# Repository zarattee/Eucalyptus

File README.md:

# Eucalyptus
 La tarjeta Eucalyptus es una placa diseñada principalmente para robots minisumos de competencia.

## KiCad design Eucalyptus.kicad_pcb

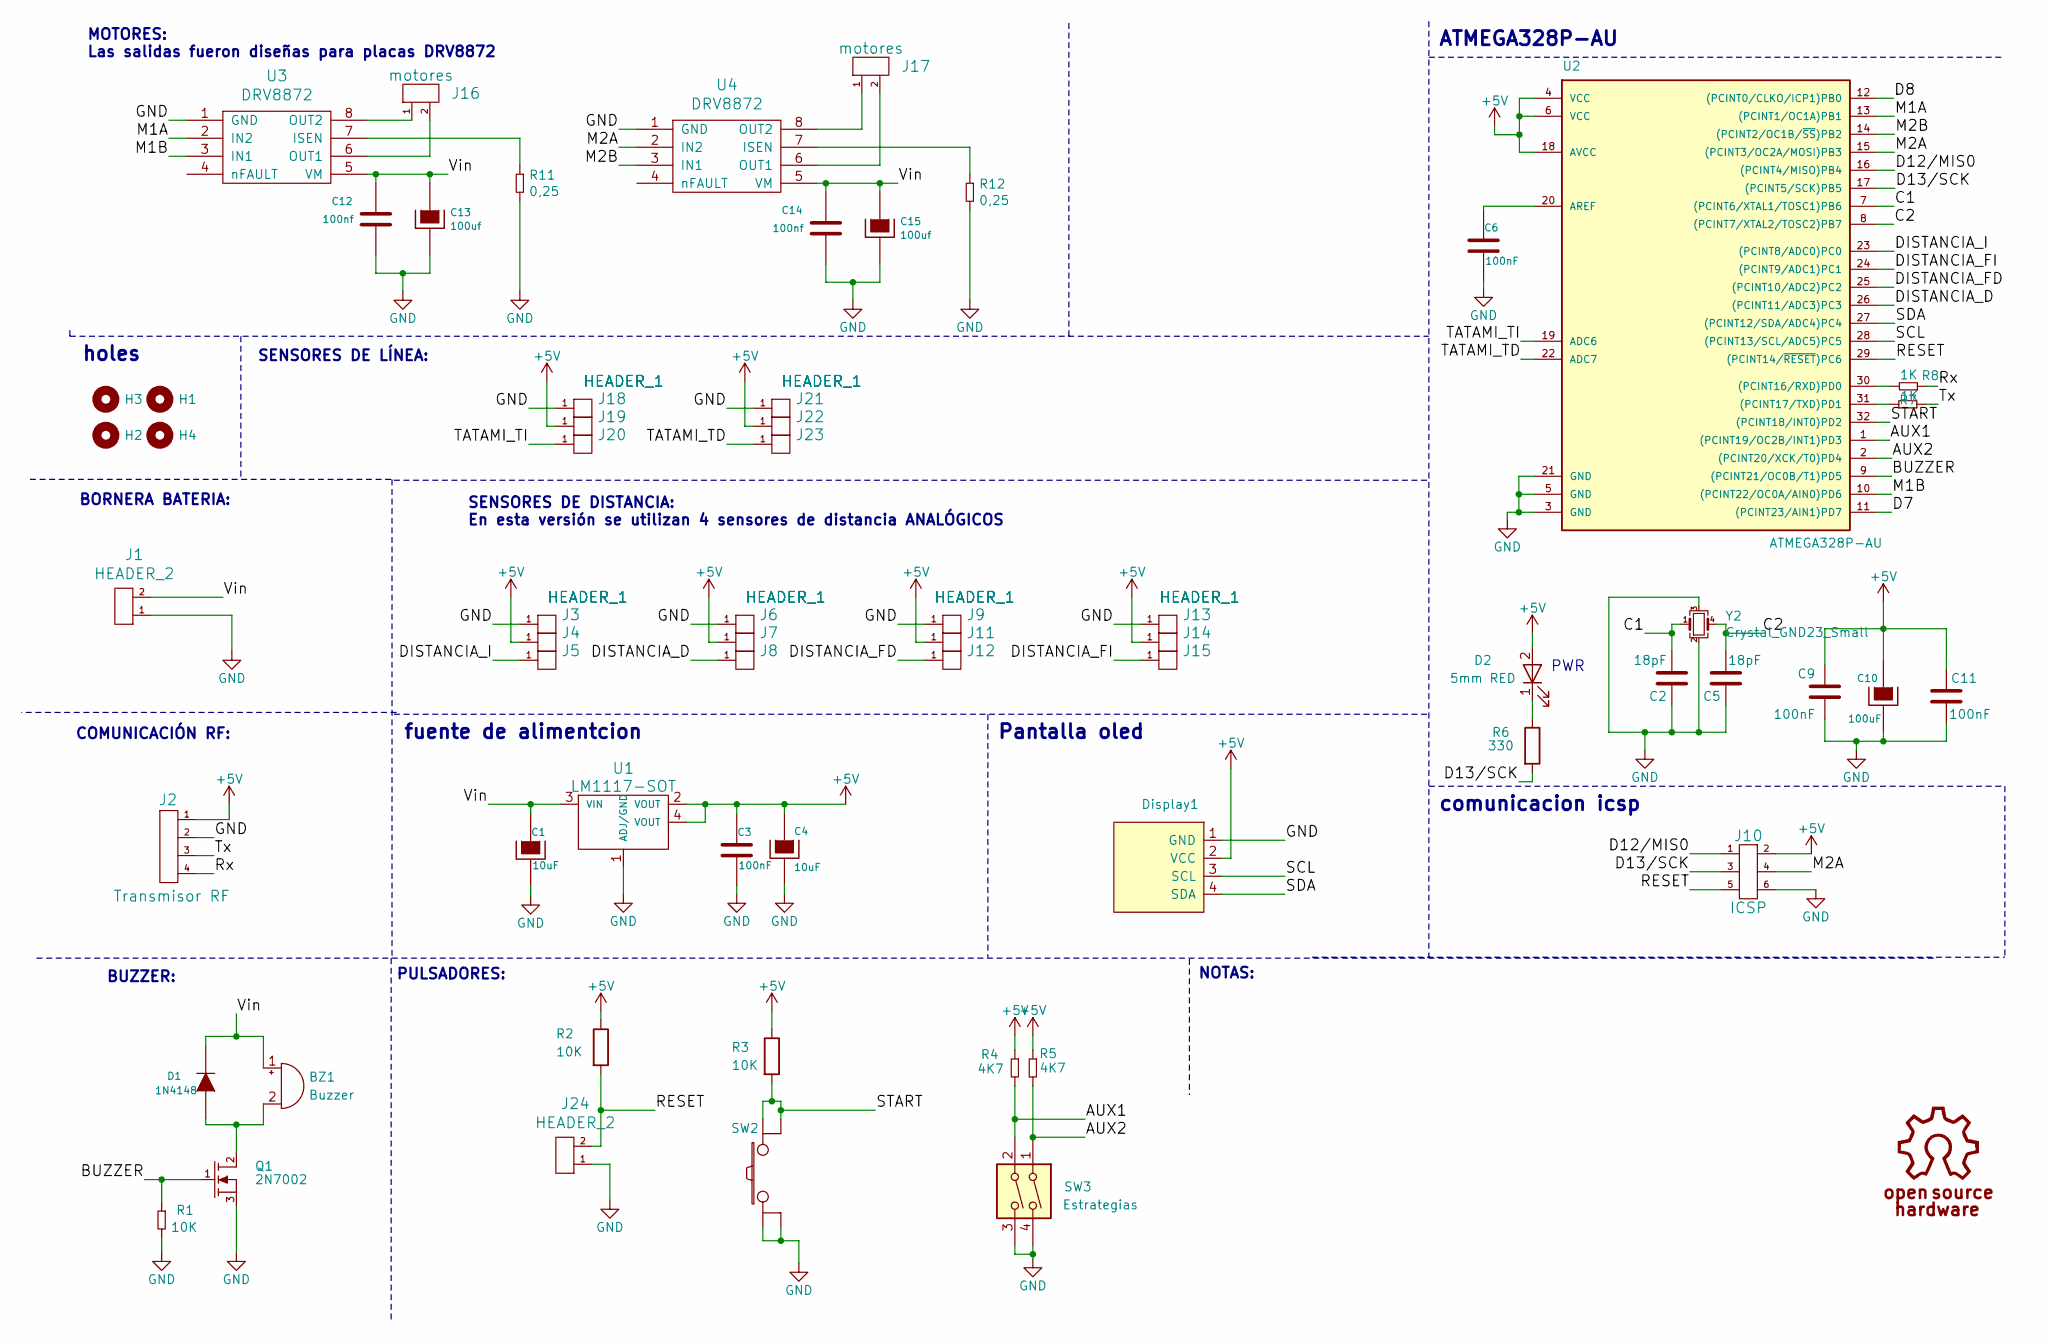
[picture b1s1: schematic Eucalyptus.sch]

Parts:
BZ1: Buzzer; Buzzer_12mm
C1, C4: 10uF; CAP_ELEC_SMD_4X5.5
C2, C5: 18pF; C_1206
C3, C6, C9, C11: 100nF; C_1206
C10: 100uF; CAP_ELEC_SMD_4X5.5
C12, C14: 100nf; C_1206
C13, C15: 100uf; CAP_ELEC_SMD_4X5.5
D1: 1N4148; SOD80C
D2: 5mm RED; LED_1206
Display1: SSD1306-SSD1306-128x64_OLED; 128x64OLED
H1, H2, H3, H4: Mounting_Hole; Separador_M3_5mm
J1: HEADER_2; JST_EH_B2B-EH-A_1x02_P2.50mm_Vertical
J2: Transmisor RF; pin_strip_4
J3, J4, J5, J6, J7, J8, J9, J11, J12, J13, J14, J15, J18, J19, J20, J21, J22, J23: HEADER_1; DUAL_PAD_TH_SMD_2x5mm
J10: ICSP; pin_strip_3x2
J16, J17: motores; JST_EH_B2B-EH-A_1x02_P2.50mm_Vertical
J24: HEADER_2; SW_SPST_EVQPE1
Q1: 2N7002; SOT23
R1, R2, R3: 10K; R_1206
R4, R5: 4K7; R_1206
R6: 330; R_1206
R7, R8: 1K; R_1206
R11, R12: 0,25; R_1206
SW2: SW_PUSH; Pulsador_TH_4
SW3: Estrategias; Dip_SW_2-300
U1: LM1117-SOT; SOT223
U2: ATMEGA328P-AU; TQFP-32_7x7mm_Pitch0.8mm
U3, U4: DRV8872; SSOP-8
Y2: Crystal_GND23_Small; Crystal_SMD_EuroQuartz_X22-4Pin_2.5x2.0mm

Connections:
+5V: C3.1, C4.1, C9.2, C10.1, C11.2, D2.2 (A), Display1.2 (VCC), J2.1, J4.1, J7.1, J10.2, J11.1, J14.1, J19.1, J22.1, R2.1, R3.1, R4.1, R5.1, U1.2 (VOUT), U1.4 (VOUT), U2.4 (VCC), U2.6 (VCC), U2.18 (AVCC)
/AUX1: R4.2, SW3.2, U2.1 ((PCINT19/OC2B/INT1)PD3)
/AUX2: R5.2, SW3.1, U2.2 ((PCINT20/XCK/T0)PD4)
/BUZZER: Q1.1 (G), R1.1, U2.9 ((PCINT21/OC0B/T1)PD5)
/C1: C2.2, U2.7 ((PCINT6/XTAL1/TOSC1)PB6), Y2.1
/C2: C5.2, U2.8 ((PCINT7/XTAL2/TOSC2)PB7), Y2.4
/D12/MIS0: J10.1, U2.16 ((PCINT4/MISO)PB4)
/D13/SCK: J10.3, R6.2, U2.17 ((PCINT5/SCK)PB5)
/DISTANCIA_D: J8.1, U2.26 ((PCINT11/ADC3)PC3)
/DISTANCIA_FD: J12.1, U2.25 ((PCINT10/ADC2)PC2)
/DISTANCIA_FI: J15.1, U2.24 ((PCINT9/ADC1)PC1)
/DISTANCIA_I: J5.1, U2.23 ((PCINT8/ADC0)PC0)
/M1A: U2.13 ((PCINT1/OC1A)PB1), U3.2 (IN2)
/M1B: U2.10 ((PCINT22/OC0A/AIN0)PD6), U3.3 (IN1)
/M2A: J10.4, U2.15 ((PCINT3/OC2A/MOSI)PB3), U4.2 (IN2)
/M2B: U2.14 ((PCINT2/OC1B/~SS~)PB2), U4.3 (IN1)
/RESET: J10.5, J24.2, R2.2, U2.29 ((PCINT14/~RESET~)PC6)
/Rx: J2.4, R8.1
/SCL: Display1.3 (SCL), U2.28 ((PCINT13/SCL/ADC5)PC5)
/SDA: Display1.4 (SDA), U2.27 ((PCINT12/SDA/ADC4)PC4)
/START: R3.2, SW2.3, SW2.4, U2.32 ((PCINT18/INT0)PD2)
/TATAMI_TD: J23.1, U2.22 (ADC7)
/TATAMI_TI: J20.1, U2.19 (ADC6)
/Tx: J2.3, R7.1
/Vin: BZ1.1 (-), C1.1, C12.1, C13.1, C14.1, C15.1, D1.2 (K), J1.2, U1.3 (VIN), U3.5 (VM), U4.5 (VM)
GND: C1.2, C2.1, C3.2, C4.2, C5.1, C6.2, C9.1, C10.2, C11.1, C12.2, C13.2, C14.2, C15.2, Display1.1 (GND), J1.1, J2.2, J3.1, J6.1, J9.1, J10.6, J13.1, J18.1, J21.1, J24.1, Q1.3 (S), R1.2, R11.2, R12.2, SW2.1, SW2.2, SW3.3, SW3.4, U1.1 (ADJ/GND), U2.3 (GND), U2.5 (GND), U2.21 (GND), U3.1 (GND), U4.1 (GND), Y2.2, Y2.3
unnamed: BZ1.2 (+), D1.1 (A), Q1.2 (D)
unnamed: C6.1, U2.20 (AREF)
unnamed: D2.1 (K), R6.1
unnamed: J16.1, U3.8 (OUT2)
unnamed: J16.2, U3.6 (OUT1)
unnamed: J17.1, U4.8 (OUT2)
unnamed: J17.2, U4.6 (OUT1)
unnamed: R7.2, U2.31 ((PCINT17/TXD)PD1)
unnamed: R8.2, U2.30 ((PCINT16/RXD)PD0)
unnamed: R11.1, U3.7 (ISEN)
unnamed: R12.1, U4.7 (ISEN)

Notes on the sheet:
NOTAS:
SENSORES DE LÍNEA:
COMUNICACIÓN RF:
SENSORES DE DISTANCIA: En esta versión se utilizan 4 sensores de distancia ANALÓGICOS
BORNERA BATERIA:
MOTORES: Las salidas fueron diseñas para placas DRV8872
PULSADORES:
PWR
BUZZER:
Pantalla oled
comunicacion icsp
ATMEGA328P-AU
fuente de alimentcion
holes

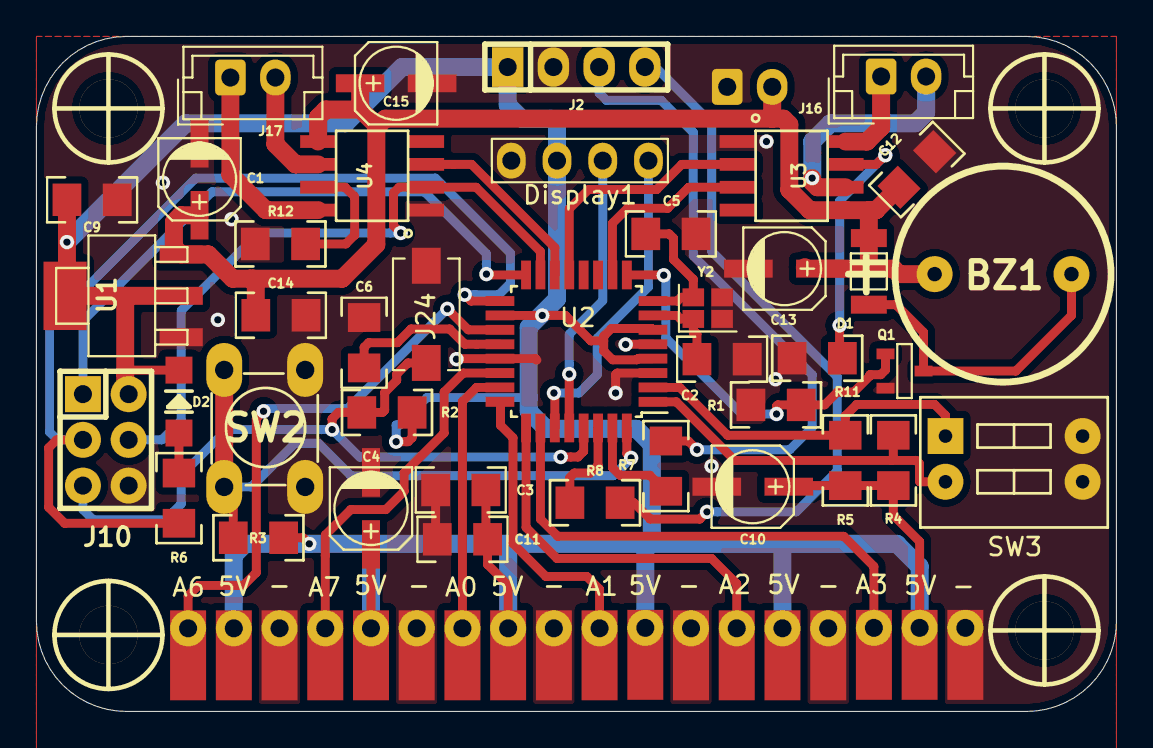
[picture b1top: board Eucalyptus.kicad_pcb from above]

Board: 2 copper layers, 60.0 x 37.5 mm, 63 parts (1 on the bottom side), 37 nets.

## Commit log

2021-01-13 modificaciones
    se empezo el sch y pcb
2021-01-14 DualPad
    Modifique y acomode los footprints de los sensores
2021-01-17 modificaciones
    se agrego pdf de sch
    pdf de lista de componentes y excel
    tambien se modifico sch y pcb
2021-01-20 MODIFICACIONES
    SE MODIFICO LISTA DE MATERIALES Y EL PCB
2021-01-27 modificaciones
    se termino el pcb, modifique el cristal en e sch, termine lista de compnentes y genere 2 imagenes de la pcb
2021-02-06 modificaciones
    se agrego logos,imagenes de referencias y se modifico serigrafia
2021-02-09 modificaciones
    se agrego archivos gerbers
2021-02-09 MODIFICACIONES
    SE MODIFICO PCB,SERIGRAFIA Y ARCHIVOS GERBERS
2021-02-12 modificaciones
    se agrego logos
